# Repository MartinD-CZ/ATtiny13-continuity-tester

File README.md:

# ATtiny13 continuity tester

*see the full article [here](http://embedblog.eu/?p=194)!*

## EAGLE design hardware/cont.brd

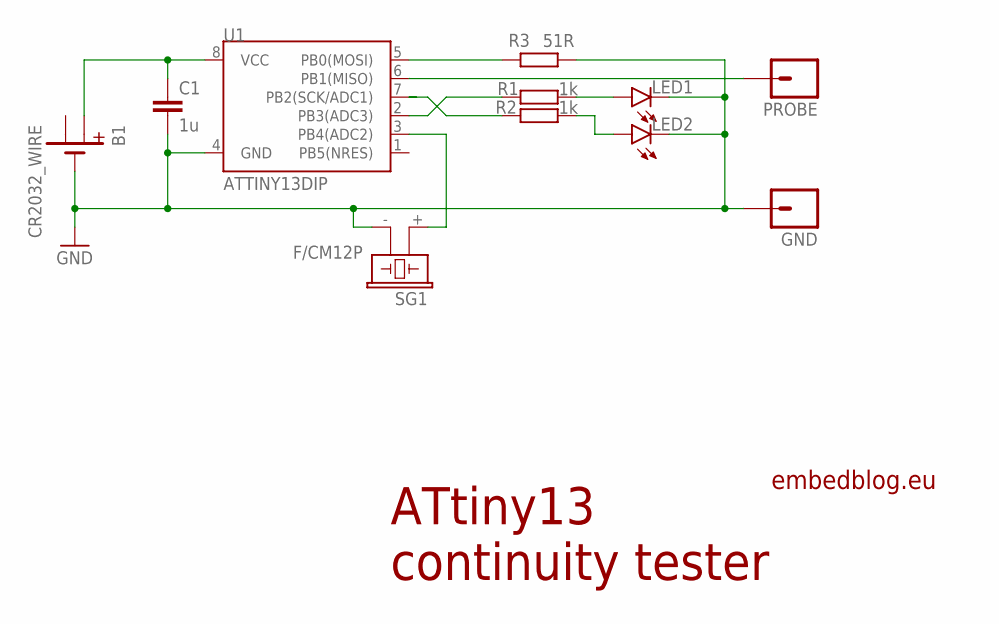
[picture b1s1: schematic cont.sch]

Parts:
B1: CR2032_WIRE; CR2032
C1: 1u; C1206
GND: M01OFFSET; 1X01_OFFSET
LED1, LED2: LEDSML1206; SML1206
PROBE: M01OFFSET; 1X01_OFFSET
R1, R2: 1k; R1206
R3: 51R; R1206
SG1: F/CM12P
U1: ATTINY13DIP; DIP08

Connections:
GND: B1.MINUS (-), C1.2, GND.1, LED1.C, LED2.C, R3.1, SG1.- (2), U1.4 (GND)
unnamed: B1.PLUS1 (+1), C1.1, U1.8 (VCC)
unnamed: R1.2, U1.2 (PB3(ADC3))
unnamed: LED1.A, R1.1
unnamed: R2.2, U1.7 (PB2(SCK/ADC1))
unnamed: LED2.A, R2.1
unnamed: R3.2, U1.5 (PB0(MOSI))
unnamed: PROBE.1, U1.6 (PB1(MISO))
unnamed: SG1.+ (1), U1.3 (PB4(ADC2))

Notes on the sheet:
ATtiny13 continuity tester
embedblog.eu

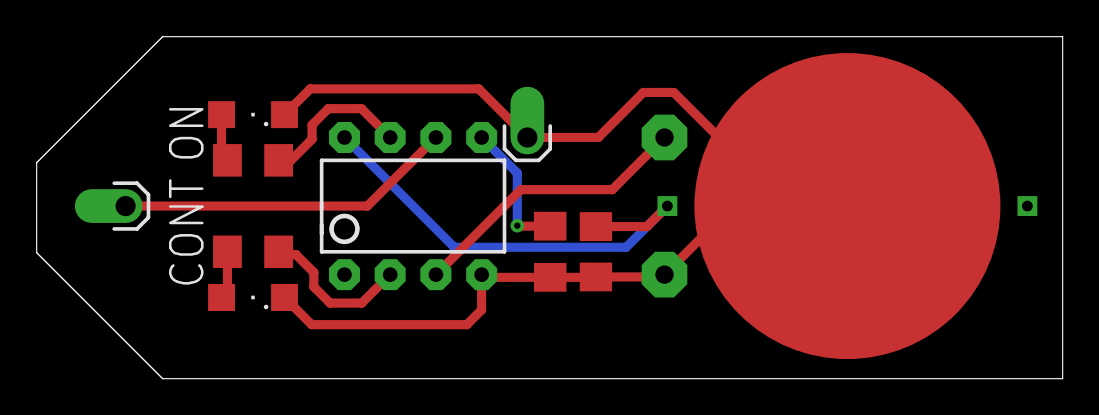
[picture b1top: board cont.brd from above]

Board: 2 copper layers, 57.0 x 19.0 mm, 11 parts (1 on the bottom side), 9 nets.

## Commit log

2019-03-26 version 1.0

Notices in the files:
parts and their libraries:
SparkFun-Connectors: Licensing: Creative Commons ShareAlike 4.0 International - https://creativecommons.org/licenses/by-sa/4.0
